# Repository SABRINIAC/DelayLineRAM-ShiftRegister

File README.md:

# Delay Line RAM (Or technically SAM)

This project is the RAM for a '60s inspired computer im making called the SABRINIAC. It is delay line ram, which means all of the bits shift in a circular loop. To read from the memory you wait for the right bits to come by (You can find out the current address its on by the 2nd pcb in this project, the address counter) and then take in those bits. to write its similar but you set the data in to the bit you want to write, and then set write enable high when the bit you want to write passes by. It will write the data in bit instead of passing the bit around again.

I made this project because I saw a video of someone programming the UNIVAC to run a minecraft server. And also, ive built digital CPUs and now I've wanted to try my hand and building one in real life, along with the components to make it work!

This build is meant to have 8 of the RAM modules and 1 address counter module, as then you can run all the ram in parallel and have it cycle 1 byte every clock tick. Allowing 256 Bytes of memory and simpler access, instead of reading data in serially.

| Part Name | Count |
|-----------|-------|
| PCB - Address counter | 1 |
| PCB - Delay Line RAM | 8 |
| 4x1 Female Pin Headers | 17 |
| 74HC08DS Quad AND Gate | 2 |
| 74HC86N Quad XOR Gate | 2 |
| 74LS175N Quad D Flip Flop | 2 |
| 2x1 Right Angle Male Pin Headers | 34 |
| 1KΩ Resistor | 64 |
| 2N2222A NPN Transistor | 24 |
| 74HC595 8Bit SIPO Shift Registers | 256 |

Note there is no LEDs or resistors for the address counter PCB, I intend to leave it unpopulated unless I need to debug. It will work just fine without those parts

# Built Modules

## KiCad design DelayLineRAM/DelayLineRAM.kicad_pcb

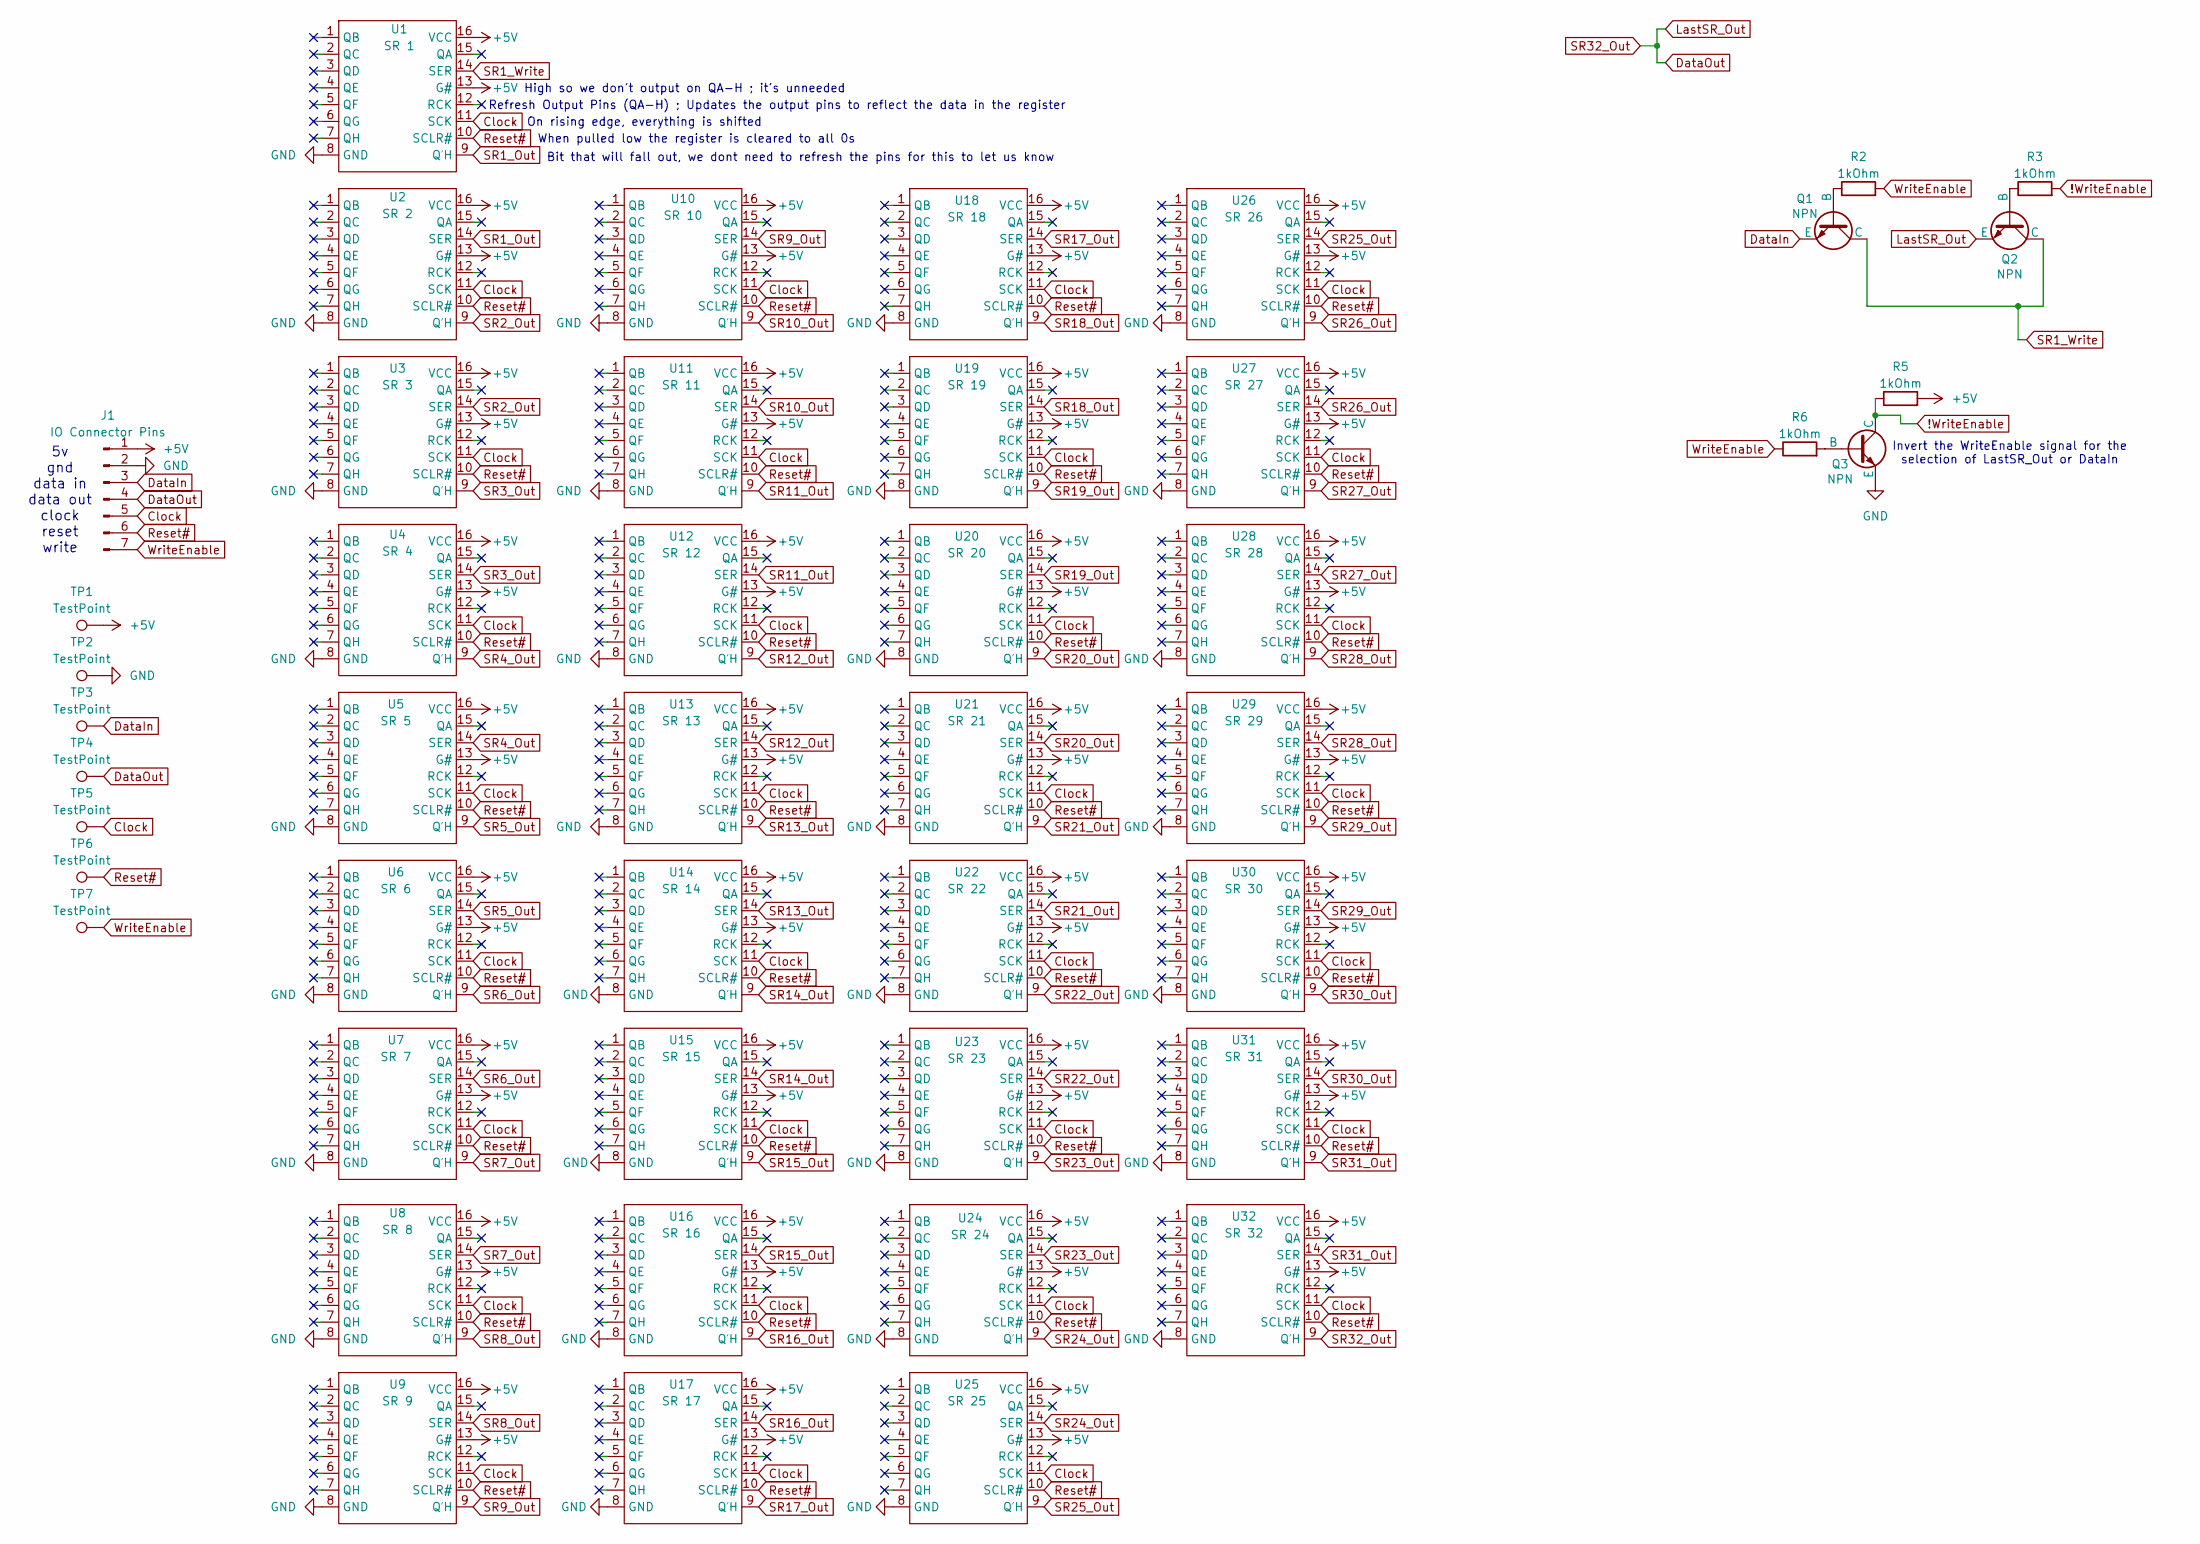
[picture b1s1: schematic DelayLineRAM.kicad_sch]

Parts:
J1: IO Connector Pins; PinHeader_1x07_P2.54mm_Horizontal
Q1, Q2, Q3: NPN; TO-92
R2, R3, R5, R6: 1kOhm; R_Axial_DIN0204_L3.6mm_D1.6mm_P5.08mm_Horizontal
TP1, TP2, TP3, TP4, TP5, TP6, TP7: TestPoint; TestPoint_Pad_D1.5mm
U1: SR 1; SOP-16_L9.9-W3.9-P1.27-LS6.0-BL; Manufacturer Part 74HC595DRG; LCSC Part Name 74系列 逻辑芯片
U2: SR 2; SOP-16_L9.9-W3.9-P1.27-LS6.0-BL; Manufacturer Part 74HC595DRG; LCSC Part Name 74系列 逻辑芯片
U3: SR 3; SOP-16_L9.9-W3.9-P1.27-LS6.0-BL; Manufacturer Part 74HC595DRG; LCSC Part Name 74系列 逻辑芯片
U4: SR 4; SOP-16_L9.9-W3.9-P1.27-LS6.0-BL; Manufacturer Part 74HC595DRG; LCSC Part Name 74系列 逻辑芯片
U5: SR 5; SOP-16_L9.9-W3.9-P1.27-LS6.0-BL; Manufacturer Part 74HC595DRG; LCSC Part Name 74系列 逻辑芯片
U6: SR 6; SOP-16_L9.9-W3.9-P1.27-LS6.0-BL; Manufacturer Part 74HC595DRG; LCSC Part Name 74系列 逻辑芯片
U7: SR 7; SOP-16_L9.9-W3.9-P1.27-LS6.0-BL; Manufacturer Part 74HC595DRG; LCSC Part Name 74系列 逻辑芯片
U8: SR 8; SOP-16_L9.9-W3.9-P1.27-LS6.0-BL; Manufacturer Part 74HC595DRG; LCSC Part Name 74系列 逻辑芯片
U9: SR 9; SOP-16_L9.9-W3.9-P1.27-LS6.0-BL; Manufacturer Part 74HC595DRG; LCSC Part Name 74系列 逻辑芯片
U10: SR 10; SOP-16_L9.9-W3.9-P1.27-LS6.0-BL; Manufacturer Part 74HC595DRG; LCSC Part Name 74系列 逻辑芯片
U11: SR 11; SOP-16_L9.9-W3.9-P1.27-LS6.0-BL; Manufacturer Part 74HC595DRG; LCSC Part Name 74系列 逻辑芯片
U12: SR 12; SOP-16_L9.9-W3.9-P1.27-LS6.0-BL; Manufacturer Part 74HC595DRG; LCSC Part Name 74系列 逻辑芯片
U13: SR 13; SOP-16_L9.9-W3.9-P1.27-LS6.0-BL; Manufacturer Part 74HC595DRG; LCSC Part Name 74系列 逻辑芯片
U14: SR 14; SOP-16_L9.9-W3.9-P1.27-LS6.0-BL; Manufacturer Part 74HC595DRG; LCSC Part Name 74系列 逻辑芯片
U15: SR 15; SOP-16_L9.9-W3.9-P1.27-LS6.0-BL; Manufacturer Part 74HC595DRG; LCSC Part Name 74系列 逻辑芯片
U16: SR 16; SOP-16_L9.9-W3.9-P1.27-LS6.0-BL; Manufacturer Part 74HC595DRG; LCSC Part Name 74系列 逻辑芯片
U17: SR 17; SOP-16_L9.9-W3.9-P1.27-LS6.0-BL; Manufacturer Part 74HC595DRG; LCSC Part Name 74系列 逻辑芯片
U18: SR 18; SOP-16_L9.9-W3.9-P1.27-LS6.0-BL; Manufacturer Part 74HC595DRG; LCSC Part Name 74系列 逻辑芯片
U19: SR 19; SOP-16_L9.9-W3.9-P1.27-LS6.0-BL; Manufacturer Part 74HC595DRG; LCSC Part Name 74系列 逻辑芯片
U20: SR 20; SOP-16_L9.9-W3.9-P1.27-LS6.0-BL; Manufacturer Part 74HC595DRG; LCSC Part Name 74系列 逻辑芯片
U21: SR 21; SOP-16_L9.9-W3.9-P1.27-LS6.0-BL; Manufacturer Part 74HC595DRG; LCSC Part Name 74系列 逻辑芯片
U22: SR 22; SOP-16_L9.9-W3.9-P1.27-LS6.0-BL; Manufacturer Part 74HC595DRG; LCSC Part Name 74系列 逻辑芯片
U23: SR 23; SOP-16_L9.9-W3.9-P1.27-LS6.0-BL; Manufacturer Part 74HC595DRG; LCSC Part Name 74系列 逻辑芯片
U24: SR 24; SOP-16_L9.9-W3.9-P1.27-LS6.0-BL; Manufacturer Part 74HC595DRG; LCSC Part Name 74系列 逻辑芯片
U25: SR 25; SOP-16_L9.9-W3.9-P1.27-LS6.0-BL; Manufacturer Part 74HC595DRG; LCSC Part Name 74系列 逻辑芯片
U26: SR 26; SOP-16_L9.9-W3.9-P1.27-LS6.0-BL; Manufacturer Part 74HC595DRG; LCSC Part Name 74系列 逻辑芯片
U27: SR 27; SOP-16_L9.9-W3.9-P1.27-LS6.0-BL; Manufacturer Part 74HC595DRG; LCSC Part Name 74系列 逻辑芯片
U28: SR 28; SOP-16_L9.9-W3.9-P1.27-LS6.0-BL; Manufacturer Part 74HC595DRG; LCSC Part Name 74系列 逻辑芯片
U29: SR 29; SOP-16_L9.9-W3.9-P1.27-LS6.0-BL; Manufacturer Part 74HC595DRG; LCSC Part Name 74系列 逻辑芯片
U30: SR 30; SOP-16_L9.9-W3.9-P1.27-LS6.0-BL; Manufacturer Part 74HC595DRG; LCSC Part Name 74系列 逻辑芯片
U31: SR 31; SOP-16_L9.9-W3.9-P1.27-LS6.0-BL; Manufacturer Part 74HC595DRG; LCSC Part Name 74系列 逻辑芯片
U32: SR 32; SOP-16_L9.9-W3.9-P1.27-LS6.0-BL; Manufacturer Part 74HC595DRG; LCSC Part Name 74系列 逻辑芯片

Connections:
!WriteEnable: Q3.1 (C), R3.2, R5.1
+5V: J1.1, R5.2, TP1.1, U1.13 (G#), U1.16 (VCC), U2.13 (G#), U2.16 (VCC), U3.13 (G#), U3.16 (VCC), U4.13 (G#), U4.16 (VCC), U5.13 (G#), U5.16 (VCC), U6.13 (G#), U6.16 (VCC), U7.13 (G#), U7.16 (VCC), U8.13 (G#), U8.16 (VCC), U9.13 (G#), U9.16 (VCC), U10.13 (G#), U10.16 (VCC), U11.13 (G#), U11.16 (VCC), U12.13 (G#), U12.16 (VCC), U13.13 (G#), U13.16 (VCC), U14.13 (G#), U14.16 (VCC), U15.13 (G#), U15.16 (VCC), U16.13 (G#), U16.16 (VCC), U17.13 (G#), U17.16 (VCC), U18.13 (G#), U18.16 (VCC), U19.13 (G#), U19.16 (VCC), U20.13 (G#), U20.16 (VCC), U21.13 (G#), U21.16 (VCC), U22.13 (G#), U22.16 (VCC), U23.13 (G#), U23.16 (VCC), U24.13 (G#), U24.16 (VCC), U25.13 (G#), U25.16 (VCC), U26.13 (G#), U26.16 (VCC), U27.13 (G#), U27.16 (VCC), U28.13 (G#), U28.16 (VCC), U29.13 (G#), U29.16 (VCC), U30.13 (G#), U30.16 (VCC), U31.13 (G#), U31.16 (VCC), U32.13 (G#), U32.16 (VCC)
Clock: J1.5, TP5.1, U1.11 (SCK), U2.11 (SCK), U3.11 (SCK), U4.11 (SCK), U5.11 (SCK), U6.11 (SCK), U7.11 (SCK), U8.11 (SCK), U9.11 (SCK), U10.11 (SCK), U11.11 (SCK), U12.11 (SCK), U13.11 (SCK), U14.11 (SCK), U15.11 (SCK), U16.11 (SCK), U17.11 (SCK), U18.11 (SCK), U19.11 (SCK), U20.11 (SCK), U21.11 (SCK), U22.11 (SCK), U23.11 (SCK), U24.11 (SCK), U25.11 (SCK), U26.11 (SCK), U27.11 (SCK), U28.11 (SCK), U29.11 (SCK), U30.11 (SCK), U31.11 (SCK), U32.11 (SCK)
DataIn: J1.3, Q1.3 (E), TP3.1
DataOut: J1.4, Q2.3 (E), TP4.1, U32.9 (Q′H)
GND: J1.2, Q3.3 (E), TP2.1, U1.8 (GND), U2.8 (GND), U3.8 (GND), U4.8 (GND), U5.8 (GND), U6.8 (GND), U7.8 (GND), U8.8 (GND), U9.8 (GND), U10.8 (GND), U11.8 (GND), U12.8 (GND), U13.8 (GND), U14.8 (GND), U15.8 (GND), U16.8 (GND), U17.8 (GND), U18.8 (GND), U19.8 (GND), U20.8 (GND), U21.8 (GND), U22.8 (GND), U23.8 (GND), U24.8 (GND), U25.8 (GND), U26.8 (GND), U27.8 (GND), U28.8 (GND), U29.8 (GND), U30.8 (GND), U31.8 (GND), U32.8 (GND)
unnamed: Q1.2 (B), R2.1
unnamed: Q2.2 (B), R3.1
unnamed: Q3.2 (B), R6.2
Reset#: J1.6, TP6.1, U1.10 (SCLR#), U2.10 (SCLR#), U3.10 (SCLR#), U4.10 (SCLR#), U5.10 (SCLR#), U6.10 (SCLR#), U7.10 (SCLR#), U8.10 (SCLR#), U9.10 (SCLR#), U10.10 (SCLR#), U11.10 (SCLR#), U12.10 (SCLR#), U13.10 (SCLR#), U14.10 (SCLR#), U15.10 (SCLR#), U16.10 (SCLR#), U17.10 (SCLR#), U18.10 (SCLR#), U19.10 (SCLR#), U20.10 (SCLR#), U21.10 (SCLR#), U22.10 (SCLR#), U23.10 (SCLR#), U24.10 (SCLR#), U25.10 (SCLR#), U26.10 (SCLR#), U27.10 (SCLR#), U28.10 (SCLR#), U29.10 (SCLR#), U30.10 (SCLR#), U31.10 (SCLR#), U32.10 (SCLR#)
SR1_Out: U1.9 (Q′H), U2.14 (SER)
SR1_Write: Q1.1 (C), Q2.1 (C), U1.14 (SER)
SR2_Out: U2.9 (Q′H), U3.14 (SER)
SR3_Out: U3.9 (Q′H), U4.14 (SER)
SR4_Out: U4.9 (Q′H), U5.14 (SER)
SR5_Out: U5.9 (Q′H), U6.14 (SER)
SR6_Out: U6.9 (Q′H), U7.14 (SER)
SR7_Out: U7.9 (Q′H), U8.14 (SER)
SR8_Out: U8.9 (Q′H), U9.14 (SER)
SR9_Out: U9.9 (Q′H), U10.14 (SER)
SR10_Out: U10.9 (Q′H), U11.14 (SER)
SR11_Out: U11.9 (Q′H), U12.14 (SER)
SR12_Out: U12.9 (Q′H), U13.14 (SER)
SR13_Out: U13.9 (Q′H), U14.14 (SER)
SR14_Out: U14.9 (Q′H), U15.14 (SER)
SR15_Out: U15.9 (Q′H), U16.14 (SER)
SR16_Out: U16.9 (Q′H), U17.14 (SER)
SR17_Out: U17.9 (Q′H), U18.14 (SER)
SR18_Out: U18.9 (Q′H), U19.14 (SER)
SR19_Out: U19.9 (Q′H), U20.14 (SER)
SR20_Out: U20.9 (Q′H), U21.14 (SER)
SR21_Out: U21.9 (Q′H), U22.14 (SER)
SR22_Out: U22.9 (Q′H), U23.14 (SER)
SR23_Out: U23.9 (Q′H), U24.14 (SER)
SR24_Out: U24.9 (Q′H), U25.14 (SER)
SR25_Out: U25.9 (Q′H), U26.14 (SER)
SR26_Out: U26.9 (Q′H), U27.14 (SER)
SR27_Out: U27.9 (Q′H), U28.14 (SER)
SR28_Out: U28.9 (Q′H), U29.14 (SER)
SR29_Out: U29.9 (Q′H), U30.14 (SER)
SR30_Out: U30.9 (Q′H), U31.14 (SER)
SR31_Out: U31.9 (Q′H), U32.14 (SER)
WriteEnable: J1.7, R2.2, R6.1, TP7.1

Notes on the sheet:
Bit that will fall out, we dont need to refresh the pins for this to let us know
5v gnd data in data out clock reset write
High so we don't output on QA-H ; it's unneeded
On rising edge, everything is shifted
When pulled low the register is cleared to all 0s
Invert the WriteEnable signal for the selection of LastSR_Out or DataIn
Refresh Output Pins (QA-H) ; Updates the output pins to reflect the data in the register

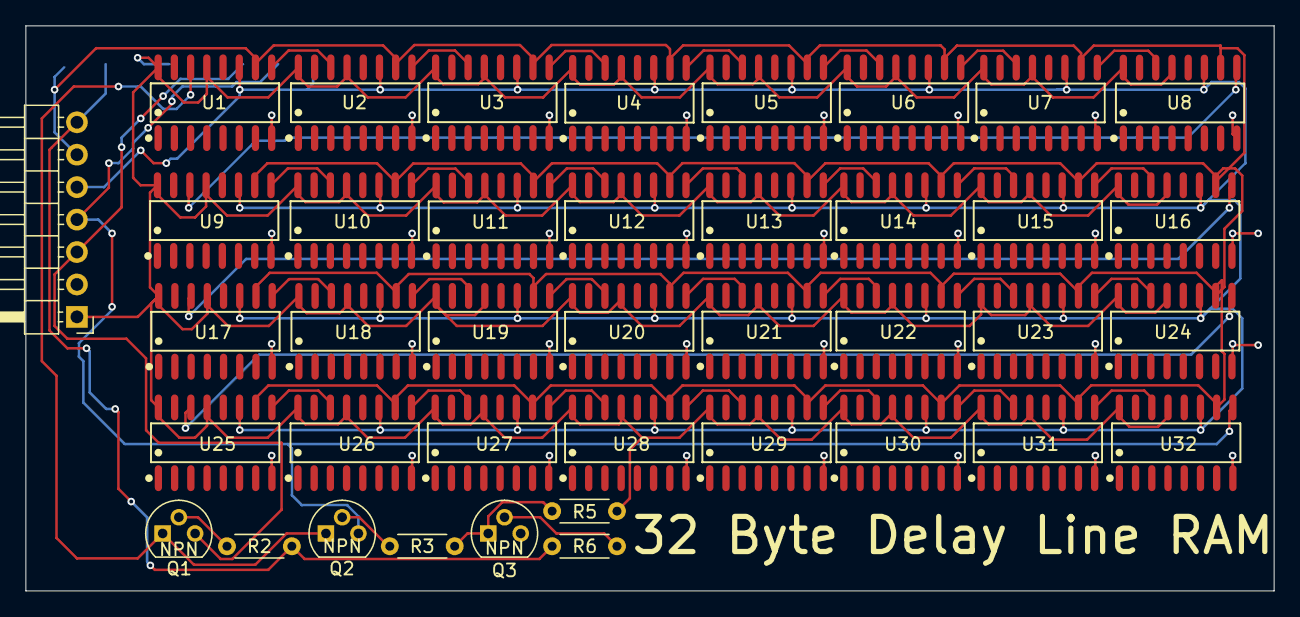
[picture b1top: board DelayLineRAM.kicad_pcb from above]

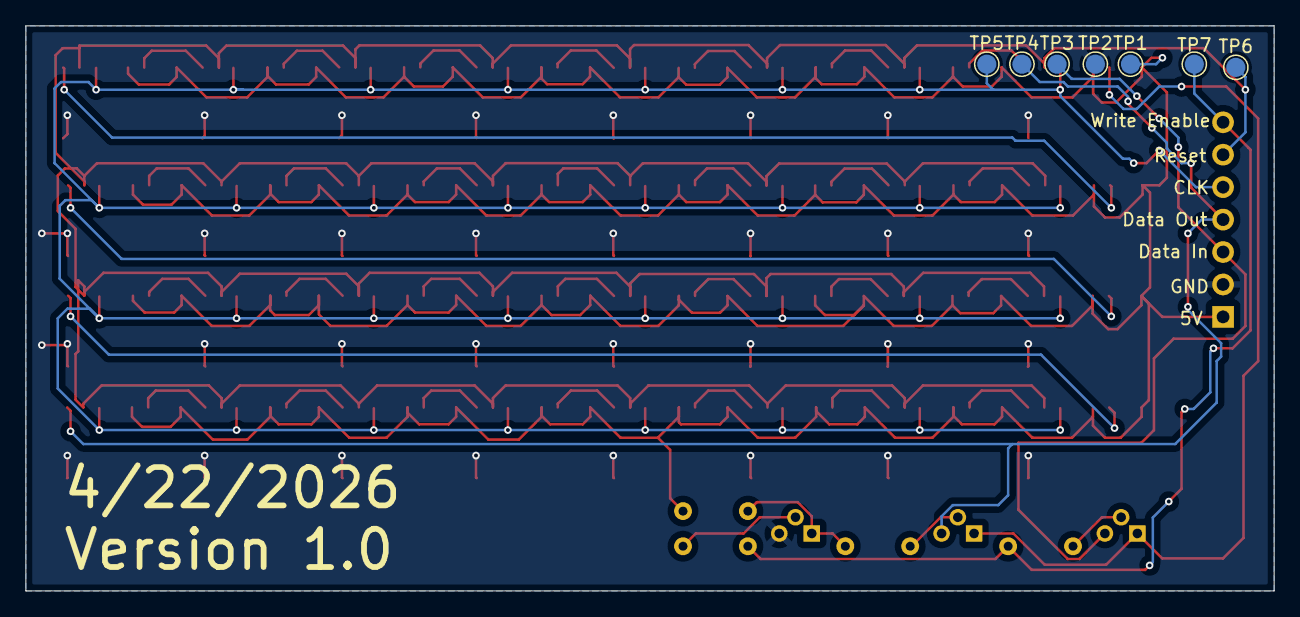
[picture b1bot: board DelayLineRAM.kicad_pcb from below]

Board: 2 copper layers, 97.8 x 44.2 mm, 47 parts (7 on the bottom side), 43 nets.

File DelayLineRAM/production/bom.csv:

Designator,Footprint,Quantity,Value,LCSC Part #
"D1, D2",D_5W_P12.70mm_Horizontal,2,D,
J1,PinHeader_1x07_P2.54mm_Horizontal,1,IO Connector Pins,
"Q1, Q2, Q3",TO-92,3,NPN,
"R1, R2, R3, R4, R5, R6",R_Axial_DIN0204_L3.6mm_D1.6mm_P5.08mm_Horizontal,6,1kOhm,
"TP1, TP2, TP3, TP4, TP5, TP6, TP7",TestPoint_Pad_D1.5mm,7,TestPoint,
U1,SOP-16_L9.9-W3.9-P1.27-LS6.0-BL,1,SR 1,
U10,SOP-16_L9.9-W3.9-P1.27-LS6.0-BL,1,SR 10,
U11,SOP-16_L9.9-W3.9-P1.27-LS6.0-BL,1,SR 11,
U12,SOP-16_L9.9-W3.9-P1.27-LS6.0-BL,1,SR 12,
U13,SOP-16_L9.9-W3.9-P1.27-LS6.0-BL,1,SR 13,
U14,SOP-16_L9.9-W3.9-P1.27-LS6.0-BL,1,SR 14,
U15,SOP-16_L9.9-W3.9-P1.27-LS6.0-BL,1,SR 15,
U16,SOP-16_L9.9-W3.9-P1.27-LS6.0-BL,1,SR 16,
U17,SOP-16_L9.9-W3.9-P1.27-LS6.0-BL,1,SR 17,
U18,SOP-16_L9.9-W3.9-P1.27-LS6.0-BL,1,SR 18,
U19,SOP-16_L9.9-W3.9-P1.27-LS6.0-BL,1,SR 19,
U2,SOP-16_L9.9-W3.9-P1.27-LS6.0-BL,1,SR 2,
U20,SOP-16_L9.9-W3.9-P1.27-LS6.0-BL,1,SR 20,
U21,SOP-16_L9.9-W3.9-P1.27-LS6.0-BL,1,SR 21,
U22,SOP-16_L9.9-W3.9-P1.27-LS6.0-BL,1,SR 22,
U23,SOP-16_L9.9-W3.9-P1.27-LS6.0-BL,1,SR 23,
U24,SOP-16_L9.9-W3.9-P1.27-LS6.0-BL,1,SR 24,
U25,SOP-16_L9.9-W3.9-P1.27-LS6.0-BL,1,SR 25,
U26,SOP-16_L9.9-W3.9-P1.27-LS6.0-BL,1,SR 26,
U27,SOP-16_L9.9-W3.9-P1.27-LS6.0-BL,1,SR 27,
U28,SOP-16_L9.9-W3.9-P1.27-LS6.0-BL,1,SR 28,
U29,SOP-16_L9.9-W3.9-P1.27-LS6.0-BL,1,SR 29,
U3,SOP-16_L9.9-W3.9-P1.27-LS6.0-BL,1,SR 3,
U30,SOP-16_L9.9-W3.9-P1.27-LS6.0-BL,1,SR 30,
U31,SOP-16_L9.9-W3.9-P1.27-LS6.0-BL,1,SR 31,
U32,SOP-16_L9.9-W3.9-P1.27-LS6.0-BL,1,SR 32,
U4,SOP-16_L9.9-W3.9-P1.27-LS6.0-BL,1,SR 4,
U5,SOP-16_L9.9-W3.9-P1.27-LS6.0-BL,1,SR 5,
U6,SOP-16_L9.9-W3.9-P1.27-LS6.0-BL,1,SR 6,
U7,SOP-16_L9.9-W3.9-P1.27-LS6.0-BL,1,SR 7,
U8,SOP-16_L9.9-W3.9-P1.27-LS6.0-BL,1,SR 8,
U9,SOP-16_L9.9-W3.9-P1.27-LS6.0-BL,1,SR 9,

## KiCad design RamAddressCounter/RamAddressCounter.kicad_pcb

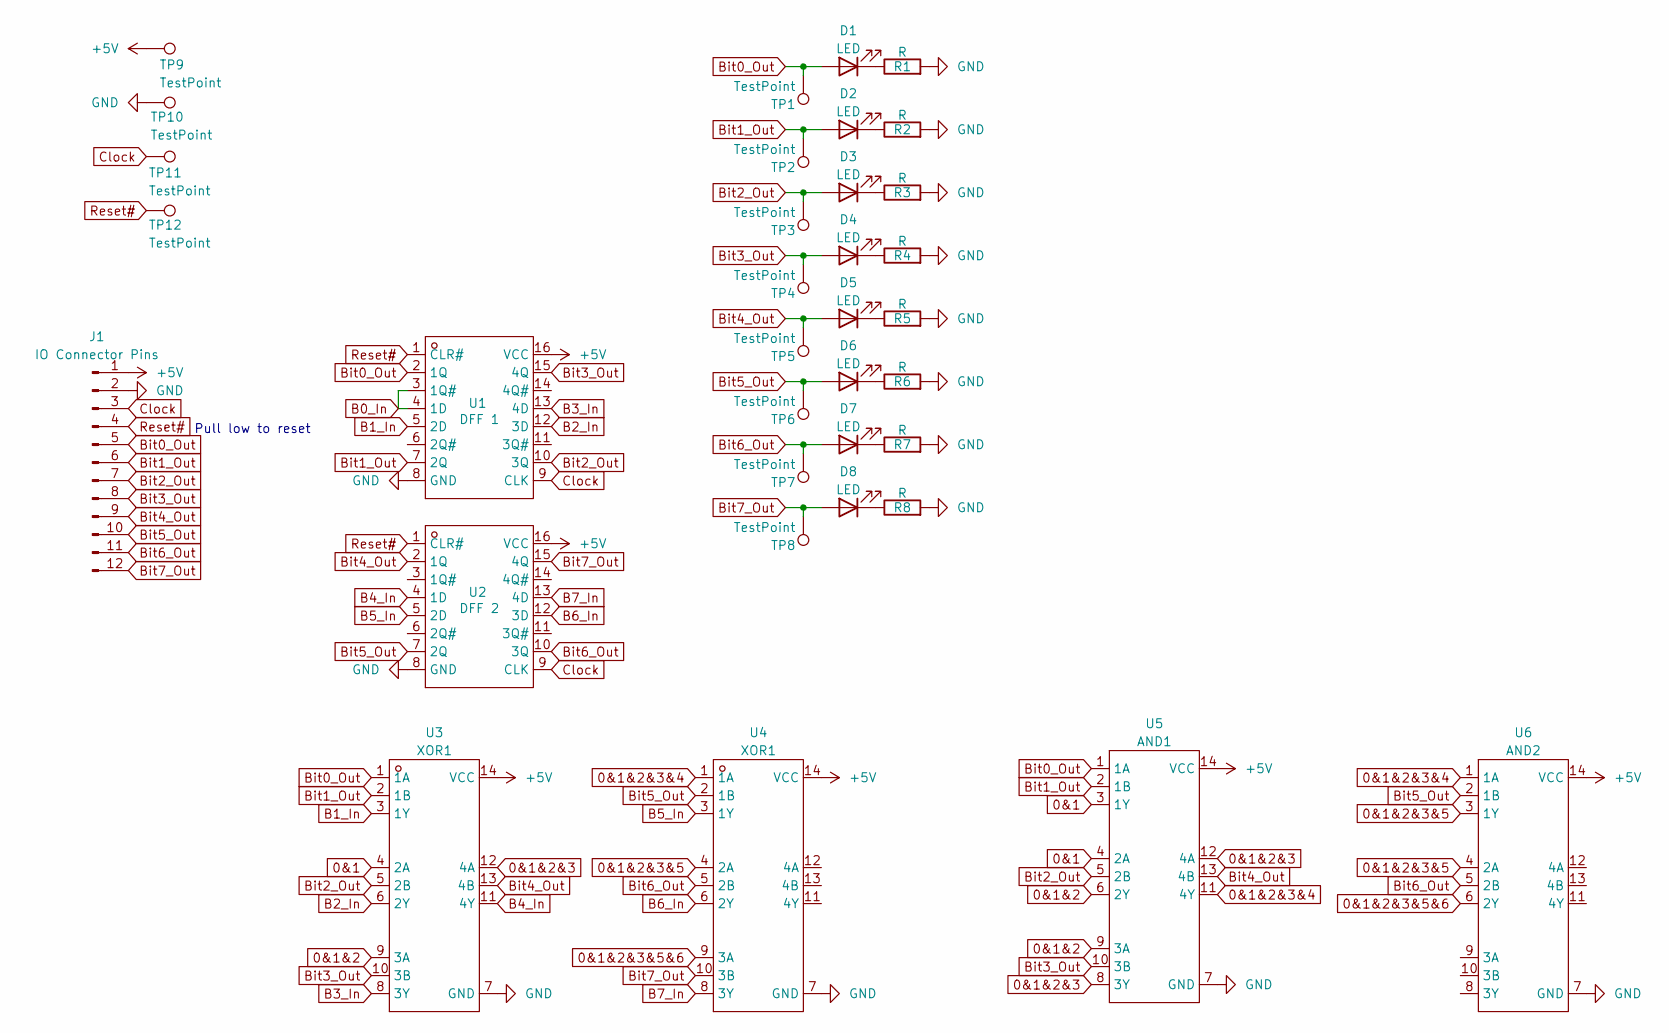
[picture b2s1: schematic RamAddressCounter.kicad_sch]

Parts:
D1, D2, D3, D4, D5, D6, D7, D8: LED; LED_D3.0mm_Clear
J1: IO Connector Pins; PinHeader_1x12_P2.54mm_Horizontal
R1, R2, R3, R4, R5, R6, R7, R8: R; R_Axial_DIN0204_L3.6mm_D1.6mm_P7.62mm_Horizontal
TP1, TP2, TP3, TP4, TP5, TP6, TP7, TP8, TP9, TP10, TP11, TP12: TestPoint; TestPoint_Pad_D1.5mm
U1: DFF 1; DIP-16_L19.3-W6.4-P2.54-LS7.6-BL; Manufacturer Part SN74LS175N; LCSC Part Name SN74LS175N
U2: DFF 2; DIP-16_L19.3-W6.4-P2.54-LS7.6-BL; Manufacturer Part SN74LS175N; LCSC Part Name SN74LS175N
U3, U4: XOR1; PDIP-14_L19.3-W6.5-P2.54-LS7.6-BL; Manufacturer Part SN74HC86N(LX); LCSC Part Name 集成电路
U5: AND1; SOP-14_L8.8-W3.9-P1.27-LS6.0-BL; Manufacturer Part SN74HC08DS; LCSC Part Name 四2输入与门
U6: AND2; SOP-14_L8.8-W3.9-P1.27-LS6.0-BL; Manufacturer Part SN74HC08DS; LCSC Part Name 四2输入与门

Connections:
0&1: U3.4 (2A), U5.3 (1Y), U5.4 (2A)
0&1&2: U3.9 (3A), U5.6 (2Y), U5.9 (3A)
0&1&2&3: U3.12 (4A), U5.8 (3Y), U5.12 (4A)
0&1&2&3&4: U4.1 (1A), U5.11 (4Y), U6.1 (1A)
0&1&2&3&5: U4.4 (2A), U6.3 (1Y), U6.4 (2A)
0&1&2&3&5&6: U4.9 (3A), U6.6 (2Y)
+5V: J1.1, TP9.1, U1.16 (VCC), U2.16 (VCC), U3.14 (VCC), U4.14 (VCC), U5.14 (VCC), U6.14 (VCC)
B0_In: U1.3 (1Q#), U1.4 (1D)
B1_In: U1.5 (2D), U3.3 (1Y)
B2_In: U1.12 (3D), U3.6 (2Y)
B3_In: U1.13 (4D), U3.8 (3Y)
B4_In: U2.4 (1D), U3.11 (4Y)
B5_In: U2.5 (2D), U4.3 (1Y)
B6_In: U2.12 (3D), U4.6 (2Y)
B7_In: U2.13 (4D), U4.8 (3Y)
Bit0_Out: D1.2 (A), J1.5, TP1.1, U1.2 (1Q), U3.1 (1A), U5.1 (1A)
Bit1_Out: D2.2 (A), J1.6, TP2.1, U1.7 (2Q), U3.2 (1B), U5.2 (1B)
Bit2_Out: D3.2 (A), J1.7, TP3.1, U1.10 (3Q), U3.5 (2B), U5.5 (2B)
Bit3_Out: D4.2 (A), J1.8, TP4.1, U1.15 (4Q), U3.10 (3B), U5.10 (3B)
Bit4_Out: D5.2 (A), J1.9, TP5.1, U2.2 (1Q), U3.13 (4B), U5.13 (4B)
Bit5_Out: D6.2 (A), J1.10, TP6.1, U2.7 (2Q), U4.2 (1B), U6.2 (1B)
Bit6_Out: D7.2 (A), J1.11, TP7.1, U2.10 (3Q), U4.5 (2B), U6.5 (2B)
Bit7_Out: D8.2 (A), J1.12, TP8.1, U2.15 (4Q), U4.10 (3B)
Clock: J1.3, TP11.1, U1.9 (CLK), U2.9 (CLK)
GND: J1.2, R1.2, R2.2, R3.2, R4.2, R5.2, R6.2, R7.2, R8.2, TP10.1, U1.8 (GND), U2.8 (GND), U3.7 (GND), U4.7 (GND), U5.7 (GND), U6.7 (GND)
unnamed: D1.1 (K), R1.1
unnamed: D2.1 (K), R2.1
unnamed: D3.1 (K), R3.1
unnamed: D4.1 (K), R4.1
unnamed: D5.1 (K), R5.1
unnamed: D6.1 (K), R6.1
unnamed: D7.1 (K), R7.1
unnamed: D8.1 (K), R8.1
Reset#: J1.4, TP12.1, U1.1 (CLR#), U2.1 (CLR#)

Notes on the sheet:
Pull low to reset

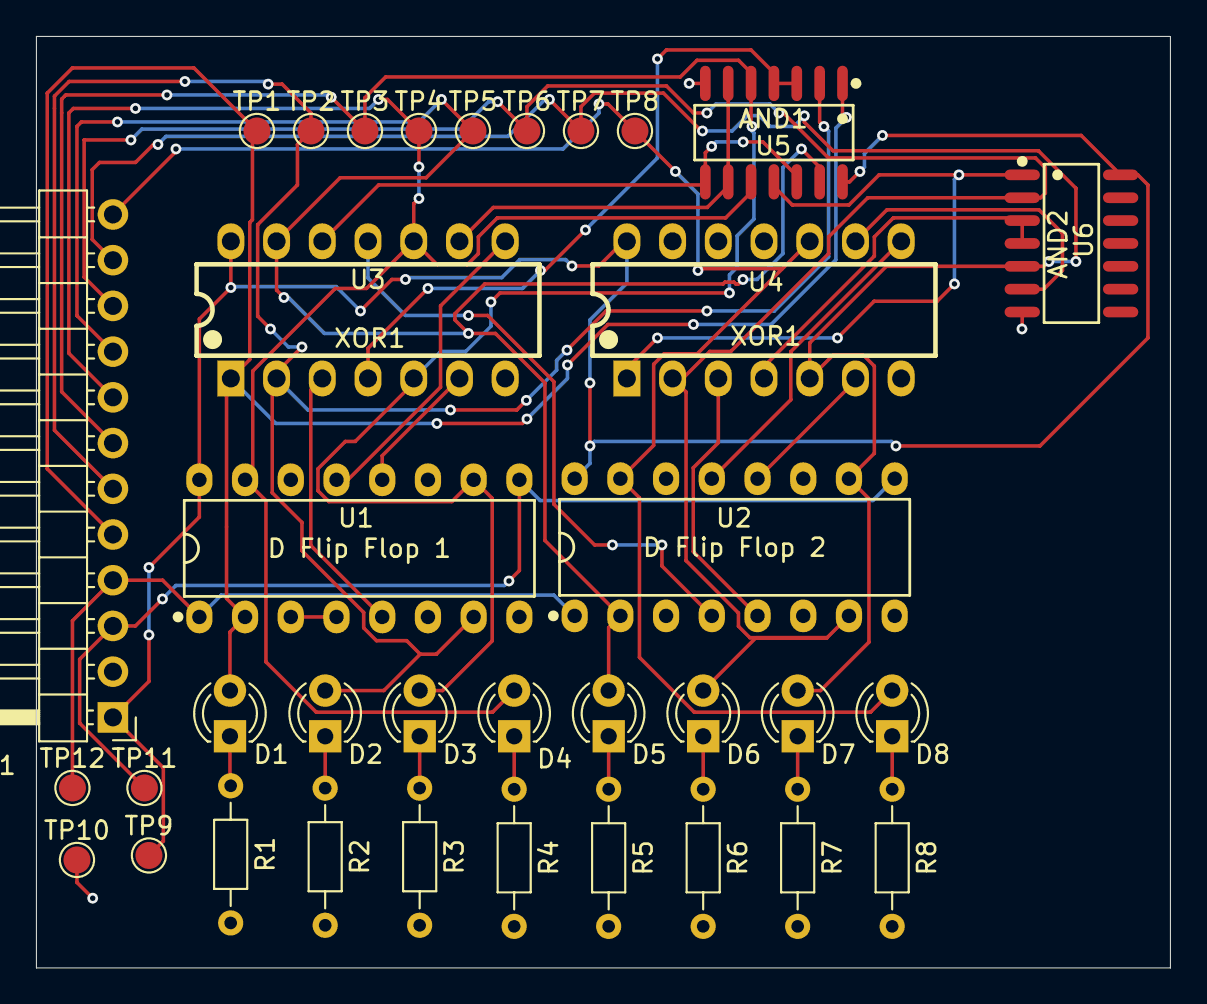
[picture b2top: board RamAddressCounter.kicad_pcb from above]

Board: 2 copper layers, 63.0 x 51.8 mm, 35 parts (0 on the bottom side), 34 nets.

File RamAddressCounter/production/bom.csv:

Designator,Footprint,Quantity,Value,LCSC Part #
"D1, D2, D3, D4, D5, D6, D7, D8",LED_D3.0mm_Clear,8,LED,
J1,PinHeader_1x12_P2.54mm_Horizontal,1,IO Connector Pins,
"R1, R2, R3, R4, R5, R6, R7, R8",R_Axial_DIN0204_L3.6mm_D1.6mm_P7.62mm_Horizontal,8,R,
"TP1, TP10, TP11, TP12, TP2, TP3, TP4, TP5, TP6, TP7, TP8, TP9",TestPoint_Pad_D1.5mm,12,TestPoint,
U1,DIP-16_L19.3-W6.4-P2.54-LS7.6-BL,1,D Flip Flop 1,
U2,DIP-16_L19.3-W6.4-P2.54-LS7.6-BL,1,D Flip Flop 2,
"U3, U4",PDIP-14_L19.3-W6.5-P2.54-LS7.6-BL,2,XOR1,
U5,SOP-14_L8.8-W3.9-P1.27-LS6.0-BL,1,AND1,
U6,SOP-14_L8.8-W3.9-P1.27-LS6.0-BL,1,AND2,

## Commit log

2026-04-22 KiCad PCB has been worked on
2026-04-23 Finished the Address Counter PCB
2026-04-23 Created fab files for the address counter
2026-04-23 removed old fab files for the dlr
2026-04-23 changed ram connector to pin headers and created fab data for the delay line ram
2026-04-23 idk kicad changed some zip files ig. backups?
2026-04-23 added a readme
2026-04-23 remove old fab files for DLR so i can update the mux line selection circuit
2026-04-23 Fixed the MUX for which data line to use when recirculating bits. Created the new FAB files for that too
2026-04-23 Uploaded an image of the completed ram pcb
2026-04-23 Fleshed out the README
2026-04-23 Fixed a count in the BOM and clarified why some components are "missing"
2026-05-16 fixed the circuit in kicad for the schem and pcb
2026-05-16 ge3nerated gerbers
2026-06-08 Added pictures of the built module to the readme
